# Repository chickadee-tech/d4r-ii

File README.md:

# Chickadee Tech D4R-II Cradle Polystack Mod #
This mod connects a FrSky D4R-II to the base control board by cradling it.

## Documentation ##
See the [wiki](https://github.com/chickadee-tech/d4r-ii/wiki) for documentation.

## Polystack ##
This **mod** board is part of the Polystack platform for modular microcontrol systems. More information on the platform can be found at [polystack.org](http://polystack.org).

## Support ##
If you need support with a board you own or have development questions please email support@chickadee.tech or check [chickadee.tech/support](https://chickadee.tech/support) for other ways to get support.

## Contributing ##
Please note that this project is released with a [Contributor Code of Conduct](CODE_OF_CONDUCT.md). By participating in this project you agree to abide by its terms.

### Setup ###
Components and footprints for PCB parts are not included in this repository. Instead, checkout the [chickadee-tech/kicad-libs](https://github.com/chickadee-tech/kicad-libs) repository in the same directory that this repository is checked out in. All part definitions should be relative so that they will load correctly.

### Pull requests ###
For fixes please submit a pull request to the original repository. After the pull request is merged, check the [Chickadee Tech Active Contributor Discount (ACD)](https://chickadee.tech/active-contributor) to see if you are eligible for a discount code to use on your next purchase.

### Derivatives ###
If developing your own version of the D4R-II cradle board please remove all Chickadee Tech trademarks and follow the [CC-BY license](LICENSE). While not required, please consider open sourcing your modifications so others can learn from your improvements. If you do, then email support@chickadee.tech and we may choose to add your project to the ACD.

You may also license the Polystack logo for free by emailing support@chickadee.tech. We'll ask for your gerbers to ensure the design complies with specifications laid out [here](https://github.com/chickadee-tech/polystack/wiki) and provide written permission to use the trademark after compliance has been demonstrated.

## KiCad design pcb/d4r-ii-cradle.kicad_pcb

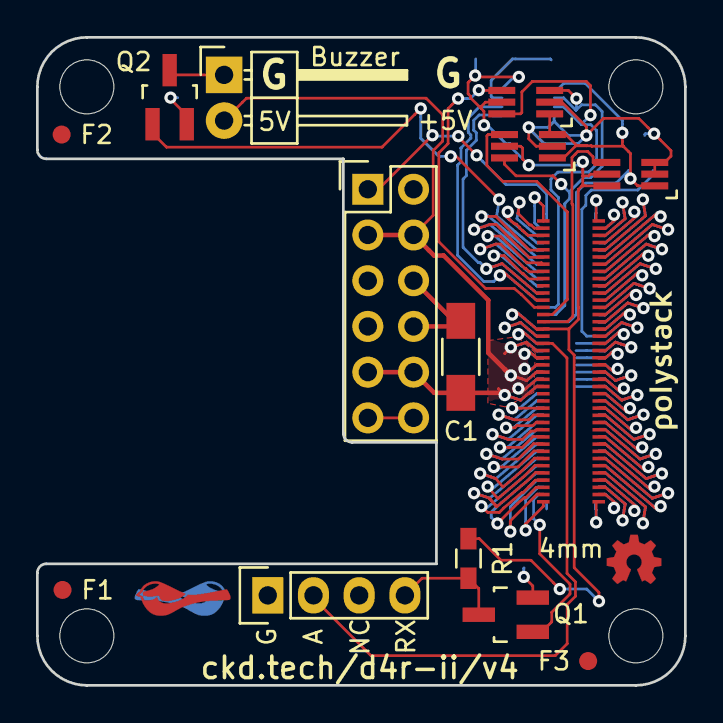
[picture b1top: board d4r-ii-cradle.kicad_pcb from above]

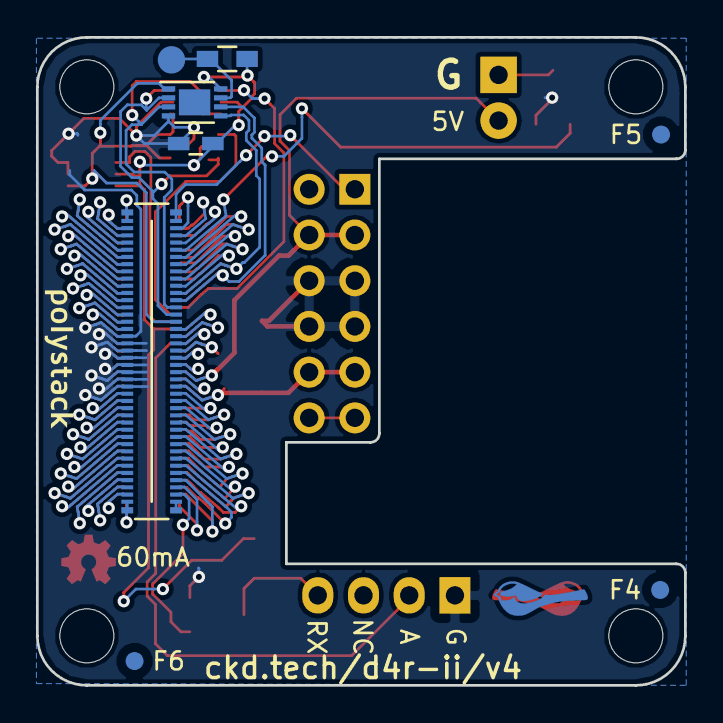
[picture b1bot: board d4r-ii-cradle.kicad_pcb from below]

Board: 2 copper layers, 36.0 x 36.0 mm, 24 parts (9 on the bottom side), 74 nets.

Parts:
C1: C; C_1206_HandSoldering
F1, F2, F3, F4, F5, F6: 1mm; Fiducial
P1: CONN_02X06; Pin_Header_Straight_2x06
P2: CONN_01X04; Pin_Header_Straight_1x04
P3: CONN_01X02; Pin_Header_Angled_1x02
PORT_ANDOR1: SN74LVC1G0832; SC-70-6_Handsoldering
PORT_C1: 0.1uF; C_0603_HandSoldering
PORT_IC1: AT24CS02-MAHM; DFN-8-1EP_3x2mm_Pitch0.5mm
PORT_IN1: CKD_SANDWICH; DF40-80pin-Header
PORT_INV1: SN74LVC1G58; SC-70-6_Handsoldering
PORT_OUT1: CKD_SANDWICH; DF40-3-4mm-80pin-Receptacle
PORT_P1: CONN_01X01; Measurement_Point_Round-SMD-Pad_Small
PORT_R1: 10k; R_0603_HandSoldering
PORT_XOR1: SN74LVC1G58; SC-70-6_Handsoldering
Q1, Q2: Q_NMOS_GSD; SOT-23_Handsoldering
R1: 10k; R_0603_HandSoldering
svg2mod, svg2mod#2: G***; polystack-bold-0.4

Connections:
+3V3: PORT_ANDOR1.5, PORT_C1.1, PORT_IC1.8, PORT_IN1.16, PORT_INV1.5, PORT_INV1.6, PORT_OUT1.16, PORT_R1.2, PORT_XOR1.5, R1.1
+5V: C1.1, P1.3, P1.4, P1.9, P1.10, P3.2, PORT_IN1.19, PORT_IN1.20, PORT_IN1.21, PORT_IN1.22, PORT_IN1.23, PORT_IN1.24, PORT_OUT1.19, PORT_OUT1.20, PORT_OUT1.21, PORT_OUT1.22, PORT_OUT1.23, PORT_OUT1.24
/ExpansionPort/3V3_0.3A_E: PORT_IN1.17, PORT_OUT1.17
/ExpansionPort/ADC1: PORT_IN1.49, PORT_OUT1.49
/ExpansionPort/ADC2: PORT_IN1.50, PORT_OUT1.50
/ExpansionPort/BATT_DIV: P2.2, PORT_IN1.18, PORT_OUT1.18
/ExpansionPort/GPIO1: PORT_IN1.5, Q2.1
/ExpansionPort/GPIO2: PORT_IN1.6, PORT_OUT1.5
/ExpansionPort/GPIO3: PORT_IN1.7, PORT_OUT1.6
/ExpansionPort/GPIO4: PORT_IN1.8, PORT_OUT1.7
/ExpansionPort/GPIO5: PORT_IN1.9, PORT_OUT1.8
/ExpansionPort/GPIO6: PORT_IN1.10, PORT_OUT1.9
/ExpansionPort/HEIGHT_1: PORT_ANDOR1.1, PORT_IC1.1, PORT_IN1.15, PORT_INV1.1, PORT_XOR1.1, PORT_XOR1.3
/ExpansionPort/HEIGHT_2: PORT_ANDOR1.3, PORT_IC1.2, PORT_IN1.14, PORT_XOR1.6
/ExpansionPort/HEIGHT_4: PORT_ANDOR1.6, PORT_IC1.3, PORT_IN1.13
/ExpansionPort/NEW_HEIGHT_1: PORT_INV1.4, PORT_OUT1.15
/ExpansionPort/NEW_HEIGHT_2: PORT_OUT1.14, PORT_XOR1.4
/ExpansionPort/NEW_HEIGHT_4: PORT_ANDOR1.4, PORT_OUT1.13
/ExpansionPort/SDMMC1_CK: PORT_IN1.55, PORT_OUT1.55
/ExpansionPort/SDMMC1_CMD: PORT_IN1.56, PORT_OUT1.56
/ExpansionPort/SDMMC1_D0: PORT_IN1.51, PORT_OUT1.51
/ExpansionPort/SDMMC1_D1: PORT_IN1.52, PORT_OUT1.52
/ExpansionPort/SDMMC1_D2: PORT_IN1.53, PORT_OUT1.53
/ExpansionPort/SDMMC1_D3: PORT_IN1.54, PORT_OUT1.54
/ExpansionPort/SPI1_MISO: PORT_IN1.79, PORT_OUT1.79
/ExpansionPort/SPI1_MOSI: PORT_IN1.80, PORT_OUT1.80
/ExpansionPort/SPI1_NSS: PORT_IN1.77, PORT_OUT1.77
/ExpansionPort/SPI1_SCK: PORT_IN1.78, PORT_OUT1.78
/ExpansionPort/SPI2_MISO: PORT_IN1.75, PORT_OUT1.75
/ExpansionPort/SPI2_MOSI: PORT_IN1.76, PORT_OUT1.76
/ExpansionPort/SPI2_NSS: PORT_IN1.73, PORT_OUT1.73
/ExpansionPort/SPI2_SCK: PORT_IN1.74, PORT_OUT1.74
/ExpansionPort/SPI3_MISO: PORT_IN1.71, PORT_OUT1.71
/ExpansionPort/SPI3_MOSI: PORT_IN1.72, PORT_OUT1.72
/ExpansionPort/SPI3_NSS: PORT_IN1.69, PORT_OUT1.69
/ExpansionPort/SPI3_SCK: PORT_IN1.70, PORT_OUT1.70
/ExpansionPort/SPI4_MISO: PORT_IN1.67, PORT_OUT1.67
/ExpansionPort/SPI4_MOSI: PORT_IN1.68, PORT_OUT1.68
/ExpansionPort/SPI4_NSS: PORT_IN1.65, PORT_OUT1.65
/ExpansionPort/SPI4_SCK: PORT_IN1.66, PORT_OUT1.66
/ExpansionPort/TIM1: P1.1, PORT_IN1.1
/ExpansionPort/TIM2: PORT_IN1.2, PORT_OUT1.1
/ExpansionPort/TIM3: PORT_IN1.3, PORT_OUT1.2
/ExpansionPort/TIM4: PORT_IN1.4, PORT_OUT1.3
/ExpansionPort/TIMG1_CH1: PORT_IN1.41, PORT_OUT1.41
/ExpansionPort/TIMG1_CH2: PORT_IN1.42, PORT_OUT1.42
/ExpansionPort/TIMG1_CH3: PORT_IN1.43, PORT_OUT1.43
/ExpansionPort/TIMG1_CH4: PORT_IN1.44, PORT_OUT1.44
/ExpansionPort/TIMG2_CH1: PORT_IN1.45, PORT_OUT1.45
/ExpansionPort/TIMG2_CH2: PORT_IN1.46, PORT_OUT1.46
/ExpansionPort/TIMG2_CH3: PORT_IN1.47, PORT_OUT1.47
/ExpansionPort/TIMG2_CH4: PORT_IN1.48, PORT_OUT1.48
/ExpansionPort/UART1_TX: PORT_IN1.39, Q1.1
/ExpansionPort/UART2_RX: PORT_IN1.38, PORT_OUT1.40
/ExpansionPort/UART2_TX: PORT_IN1.37, PORT_OUT1.39
/ExpansionPort/UART3_RX: PORT_IN1.36, PORT_OUT1.38
/ExpansionPort/UART3_TX: PORT_IN1.35, PORT_OUT1.37
/ExpansionPort/UART4_RX: PORT_IN1.34, PORT_OUT1.36
/ExpansionPort/UART4_TX: PORT_IN1.33, PORT_OUT1.35
/ExpansionPort/UART5_RX: PORT_IN1.32, PORT_OUT1.34
/ExpansionPort/UART5_TX: PORT_IN1.31, PORT_OUT1.33
/ExpansionPort/UART6_RX: PORT_IN1.30, PORT_OUT1.32
/ExpansionPort/UART6_TX: PORT_IN1.29, PORT_OUT1.31
/ExpansionPort/UART7_RX: PORT_IN1.28, PORT_OUT1.30
/ExpansionPort/UART7_TX: PORT_IN1.27, PORT_OUT1.29
/ExpansionPort/UART8_RX: PORT_IN1.26, PORT_OUT1.28
/ExpansionPort/UART8_TX: PORT_IN1.25, PORT_OUT1.27
/ExpansionPort/i2c_SCL: PORT_IC1.6, PORT_IN1.12, PORT_OUT1.12
/ExpansionPort/i2c_SDA: PORT_IC1.5, PORT_IN1.11, PORT_OUT1.11
/nTELEM: P2.4, Q1.3, R1.2
GNDPWR: C1.2, P1.5, P1.6, P1.7, P1.8, P2.1, PORT_ANDOR1.2, PORT_C1.2, PORT_IC1.4, PORT_IN1.57, PORT_IN1.58, PORT_IN1.59, PORT_IN1.60, PORT_IN1.61, PORT_IN1.62, PORT_IN1.63, PORT_IN1.64, PORT_INV1.2, PORT_INV1.3, PORT_OUT1.57, PORT_OUT1.58, PORT_OUT1.59, PORT_OUT1.60, PORT_OUT1.61, PORT_OUT1.62, PORT_OUT1.63, PORT_OUT1.64, PORT_XOR1.2, Q1.2, Q2.2
unnamed: P1.11, P1.12
unnamed: P3.1, Q2.3
unnamed: PORT_IC1.7, PORT_P1.1, PORT_R1.1

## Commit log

2015-11-11 Cradle for a D4R-II v1.
2016-02-06 v2 of D4R-II cradle that adds telemetry inverter and buzzer
2016-03-05 D4R-II v2 which adds telemetry inverter and buzzer pins.
    Also adds holes for the rest of the telemetry connector.
2016-04-13 Rebrand everything to Polystack and increment versions.
2016-04-16 Final gerbers for test manufacturing run.
2016-06-07 Update polystack logo to bold variant and bump version number.
2016-07-07 Add license information to many files. PCB design files are CC-BY and code is MIT license.
2016-07-07 Add back .gitignore after repo split.
2016-07-07 Convert to relative component and footprint paths.

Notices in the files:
pcb/d4r-ii-cradle.kicad_pcb:
Copyright 2016 Chickadee Tech LLC,
This work is licensed under the Creative Commons Attribution 4.0 International License.
To view a copy of this license, visit http://creativecommons.org/licenses/by/4.0
or send a letter to Creative Commons, PO Box 1866, Mountain View, CA 94042, USA.
